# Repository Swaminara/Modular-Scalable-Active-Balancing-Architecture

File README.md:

# Modular-Scalable-Active-Balancing-Architecture

This repository contains the PCB design files of a modular scalable active cell balancing architecture proposed during my tenure as Research Associate in TUM CREATE. 

The PCBs are designed using Easily Accessible Graphical Layout Editor (EAGLE) 7.1.0 for windows. 
However, other versions of the software shall also be used for viewing and further modifying the design.

Scientific journals supporting the repository and explaining its working principle are submitted and under review process.

This repository is protected under the MIT license as attached in the repository.

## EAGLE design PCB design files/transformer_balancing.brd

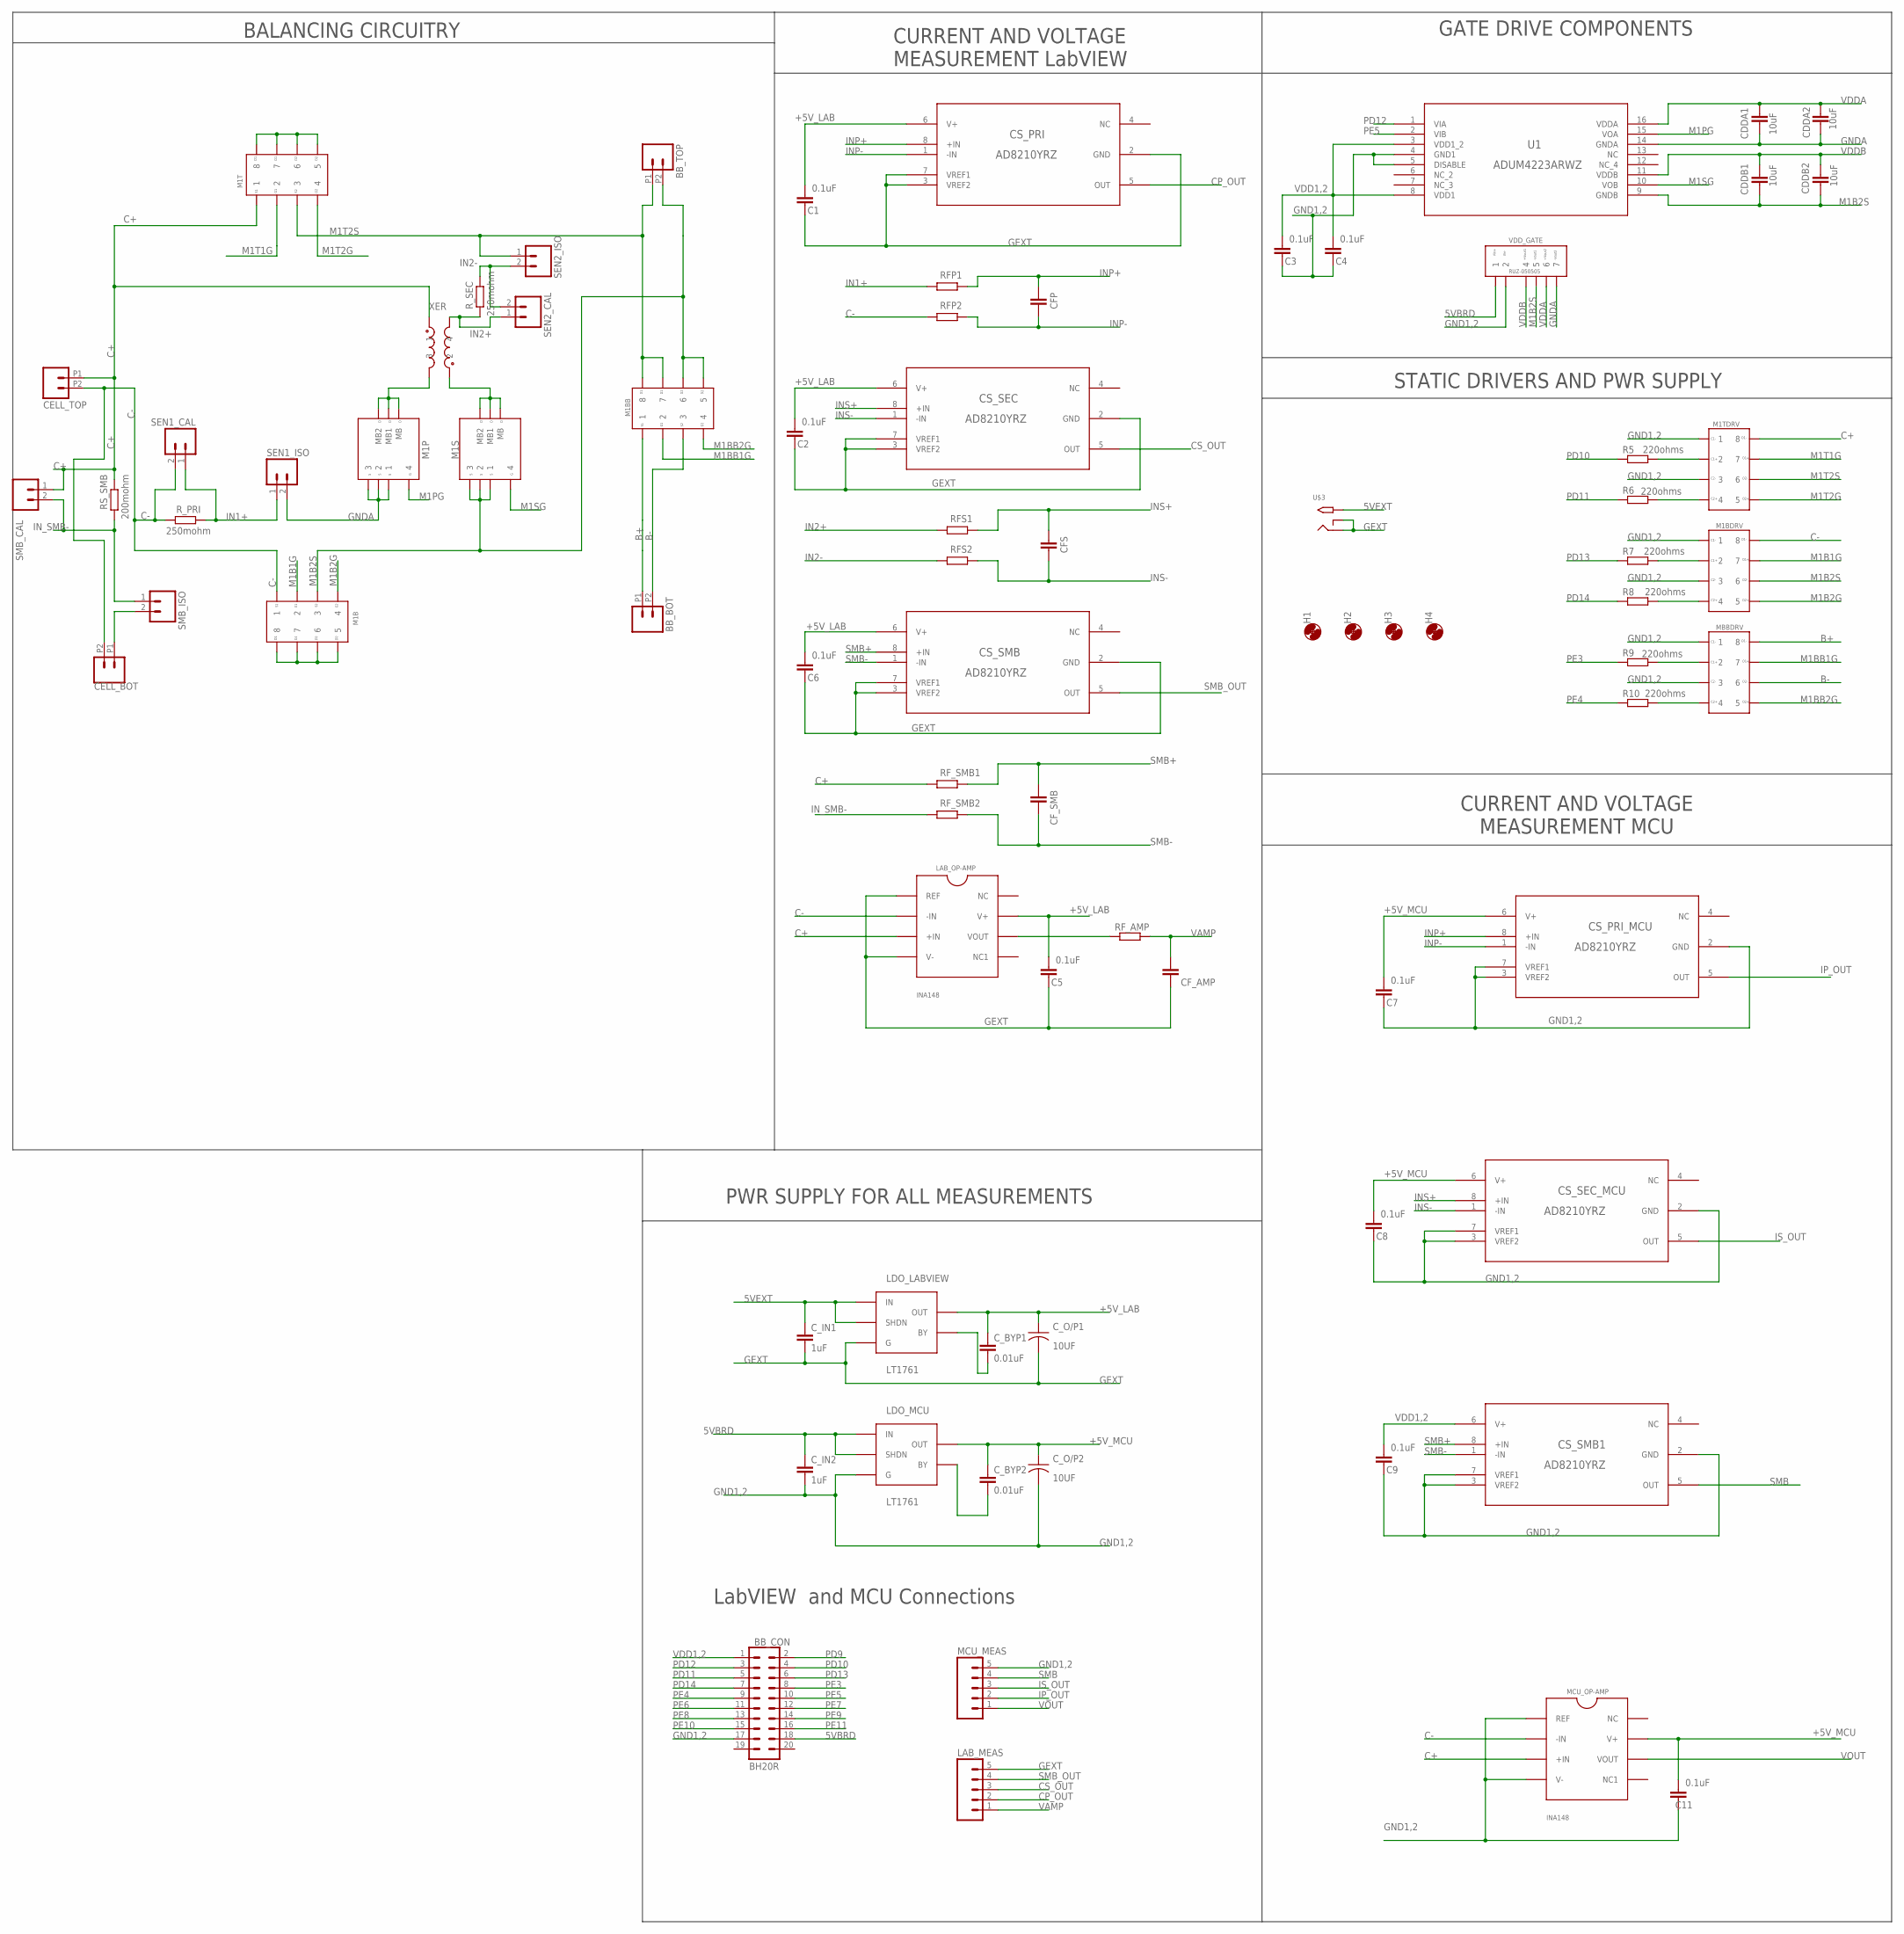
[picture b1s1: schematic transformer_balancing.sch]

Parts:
BB_BOT: M022.54MM_SCREWTERM; 1X02_2.54_SCREWTERM
BB_CON: BH20R
BB_TOP: M022.54MM_SCREWTERM; 1X02_2.54_SCREWTERM
C1, C2, C3, C4, C5, C6, C7, C8, C9, C11: 0.1uF; C0603
CDDA1, CDDA2: 10uF; C0603
CDDB1, CDDB2: 10uF; C0603
CELL_BOT: M022.54MM_SCREWTERM; 1X02_2.54_SCREWTERM
CELL_TOP: M022.54MM_SCREWTERM; 1X02_2.54_SCREWTERM
CFP: C-EUC0603; C0603
CFS: C-EUC0603; C0603
CF_AMP: C-EUC0603; C0603
CF_SMB: C-EUC0603; C0603
CS_PRI: AD8210YRZ; R_8
CS_PRI_MCU: AD8210YRZ; R_8
CS_SEC: AD8210YRZ; R_8
CS_SEC_MCU: AD8210YRZ; R_8
CS_SMB, CS_SMB1: AD8210YRZ; R_8
C_BYP1, C_BYP2: 0.01uF; C0402
C_IN1, C_IN2: 1uF; C0402
C_O/P1, C_O/P2: 10UF; 10UF_O/P_CAP_LDO
H1, H2, H3, H4: MOUNT-HOLE3.0; 3,0
LAB_MEAS: M05PTH; 1X05
LAB_OP-AMP: INA148
LDO_LABVIEW: LT1761
LDO_MCU: LT1761
M1B, M1BB, M1T: 2_CHANNEL_MOSFET
M1BDRV, M1TDRV: VOA1263
M1P, M1S: SWITCHING_MOSFET
MBBDRV: VOA1263
MCU_MEAS: M05PTH; 1X05
MCU_OP-AMP: INA148
R5, R6, R7, R8, R9, R10: 220ohms; R0603
RFP1, RFP2: 5R; R0603
RFS1, RFS2: 5R; R0603
RF_AMP: R-EU_R0603; R0603
RF_SMB1, RF_SMB2: 5R; R0603
RS_SMB: 200mohm; R0603
R_PRI: 250mohm; R0603
R_SEC: 250mohm; R0603
SEN1_CAL, SEN1_ISO, SEN2_CAL, SEN2_ISO: M02PTH; 1X02
SMB_CAL: M02PTH; 1X02
SMB_ISO: M02PTH; 1X02
U1: ADUM4223ARWZ; RW_16
U$3: 2.1MMJACK; PJ-102A
VDD_GATE: RUZ-050505
XER: COUPLED_INDUCTOR

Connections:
5VBRD: BB_CON.18, C_IN2.1, LDO_MCU.1 (IN), LDO_MCU.3 (SHDN), VDD_GATE.1
5VEXT: C_IN1.1, LDO_LABVIEW.1 (IN), LDO_LABVIEW.3 (SHDN), U$3.TIP
+5V_LAB: C1.1, C2.1, C5.1, C6.1, CS_PRI.6 (V+), CS_SEC.6 (V+), CS_SMB.6 (V+), C_BYP1.1, C_O/P1.1 (3), LAB_OP-AMP.V+, LDO_LABVIEW.5 (OUT)
+5V_MCU: C7.1, C8.1, C11.1, CS_PRI_MCU.6 (V+), CS_SEC_MCU.6 (V+), C_BYP2.1, C_O/P2.1 (3), LDO_MCU.5 (OUT), MCU_OP-AMP.V+
B+: BB_BOT.P1 (1), M1BB.1, MBBDRV.8
B-: BB_BOT.P2 (2), M1BB.3, MBBDRV.6
C+: CELL_TOP.P1 (1), LAB_OP-AMP.+IN, M1T.1, M1TDRV.8, MCU_OP-AMP.+IN, RF_SMB1.1, RS_SMB.1, SMB_CAL.1, XER.1
C-: CELL_BOT.P2 (2), CELL_TOP.P2 (2), LAB_OP-AMP.-IN, M1B.1, M1BDRV.8, MCU_OP-AMP.-IN, RFP2.1, R_PRI.2, SEN1_CAL.2
CP_OUT: CS_PRI.5 (OUT), LAB_MEAS.2
CS_OUT: CS_SEC.5 (OUT), LAB_MEAS.3
GEXT: C1.2, C2.2, C5.2, C6.2, CF_AMP.2, CS_PRI.2 (GND), CS_PRI.3 (VREF2), CS_PRI.7 (VREF1), CS_SEC.2 (GND), CS_SEC.3 (VREF2), CS_SEC.7 (VREF1), CS_SMB.2 (GND), CS_SMB.3 (VREF2), CS_SMB.7 (VREF1), C_IN1.2, C_O/P1.2 (4), LAB_MEAS.5, LAB_OP-AMP.REF, LAB_OP-AMP.V-, LDO_LABVIEW.2 (G), U$3.RING, U$3.RING_SW
GND1,2: BB_CON.17, C3.2, C4.2, C7.2, C8.2, C9.2, C11.2, CS_PRI_MCU.2 (GND), CS_PRI_MCU.3 (VREF2), CS_PRI_MCU.7 (VREF1), CS_SEC_MCU.2 (GND), CS_SEC_MCU.3 (VREF2), CS_SEC_MCU.7 (VREF1), CS_SMB1.2 (GND), CS_SMB1.3 (VREF2), CS_SMB1.7 (VREF1), C_IN2.2, C_O/P2.2 (4), LDO_MCU.2 (G), M1BDRV.1, M1BDRV.3, M1TDRV.1, M1TDRV.3, MBBDRV.1, MBBDRV.3, MCU_MEAS.5, MCU_OP-AMP.REF, MCU_OP-AMP.V-, U1.4 (GND1), U1.5 (DISABLE), VDD_GATE.2
GNDA: CDDA1.2, CDDA2.2, M1P.1, M1P.2, M1P.3, SEN1_ISO.2, U1.14 (GNDA), VDD_GATE.7
IN1+: RFP1.1, R_PRI.1, SEN1_CAL.1, SEN1_ISO.1
IN2+: RFS1.1, R_SEC.2, SEN2_CAL.1, XER.4
IN2-: RFS2.1, R_SEC.1, SEN2_CAL.2, SEN2_ISO.2
INP+: CFP.1, CS_PRI.8 (+IN), CS_PRI_MCU.8 (+IN), RFP1.2
INP-: CFP.2, CS_PRI.1 (-IN), CS_PRI_MCU.1 (-IN), RFP2.2
INS+: CFS.1, CS_SEC.8 (+IN), CS_SEC_MCU.8 (+IN), RFS1.2
INS-: CFS.2, CS_SEC.1 (-IN), CS_SEC_MCU.1 (-IN), RFS2.2
IN_SMB-: RF_SMB2.1, RS_SMB.2, SMB_CAL.2, SMB_ISO.1
IP_OUT: CS_PRI_MCU.5 (OUT), MCU_MEAS.2
IS_OUT: CS_SEC_MCU.5 (OUT), MCU_MEAS.3
M1B1G: M1B.2, M1BDRV.7
M1B2G: M1B.4, M1BDRV.5
M1B2S: BB_TOP.P2 (2), CDDB1.2, CDDB2.2, M1B.3, M1BB.5, M1BB.6, M1BDRV.6, M1S.1, M1S.2, M1S.3, U1.9 (GNDB), VDD_GATE.5
M1BB1G: M1BB.2, MBBDRV.7
M1BB2G: M1BB.4, MBBDRV.5
M1PG: M1P.4, U1.15 (VOA)
M1SG: M1S.4, U1.10 (VOB)
M1T1G: M1T.2, M1TDRV.7
M1T2G: M1T.4, M1TDRV.5
M1T2S: BB_TOP.P1 (1), M1BB.7, M1BB.8, M1T.3, M1TDRV.6, SEN2_ISO.1
unnamed: M1T.5, M1T.6, M1T.7, M1T.8
unnamed: M1TDRV.2, R5.2
unnamed: M1P.MB, M1P.MB1, M1P.MB2, XER.3
unnamed: M1TDRV.4, R6.2
unnamed: M1B.5, M1B.6, M1B.7, M1B.8
unnamed: MBBDRV.2, R9.2
unnamed: M1S.MB, M1S.MB1, M1S.MB2, XER.2
unnamed: MBBDRV.4, R10.2
unnamed: M1BDRV.4, R8.2
unnamed: LAB_OP-AMP.VOUT, RF_AMP.1
unnamed: M1BDRV.2, R7.2
unnamed: CELL_BOT.P1 (1), SMB_ISO.2
unnamed: C_BYP1.2, LDO_LABVIEW.4 (BY)
unnamed: C_BYP2.2, LDO_MCU.4 (BY)
PD9: BB_CON.2
PD10: BB_CON.4, R5.1
PD11: BB_CON.5, R6.1
PD12: BB_CON.3, U1.1 (VIA)
PD13: BB_CON.6, R7.1
PD14: BB_CON.7, R8.1
PE3: BB_CON.8, R9.1
PE4: BB_CON.9, R10.1
PE5: BB_CON.10, U1.2 (VIB)
PE6: BB_CON.11
PE7: BB_CON.12
PE8: BB_CON.13
PE9: BB_CON.14
PE10: BB_CON.15
PE11: BB_CON.16
SMB: CS_SMB1.5 (OUT), MCU_MEAS.4
SMB+: CF_SMB.1, CS_SMB.8 (+IN), CS_SMB1.8 (+IN), RF_SMB1.2
SMB-: CF_SMB.2, CS_SMB.1 (-IN), CS_SMB1.1 (-IN), RF_SMB2.2
SMB_OUT: CS_SMB.5 (OUT), LAB_MEAS.4
VAMP: CF_AMP.1, LAB_MEAS.1, RF_AMP.2
VDD1,2: BB_CON.1, C3.1, C4.1, C9.1, CS_SMB1.6 (V+), U1.3 (VDD1_2), U1.8 (VDD1)
VDDA: CDDA1.1, CDDA2.1, U1.16 (VDDA), VDD_GATE.6
VDDB: CDDB1.1, CDDB2.1, U1.11 (VDDB), VDD_GATE.4
VOUT: MCU_MEAS.1, MCU_OP-AMP.VOUT

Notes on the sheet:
BALANCING CIRCUITRY
CURRENT AND VOLTAGE MEASUREMENT LabVIEW
GATE DRIVE COMPONENTS
STATIC DRIVERS AND PWR SUPPLY
LabVIEW and MCU Connections
PWR SUPPLY FOR ALL MEASUREMENTS
CURRENT AND VOLTAGE MEASUREMENT MCU

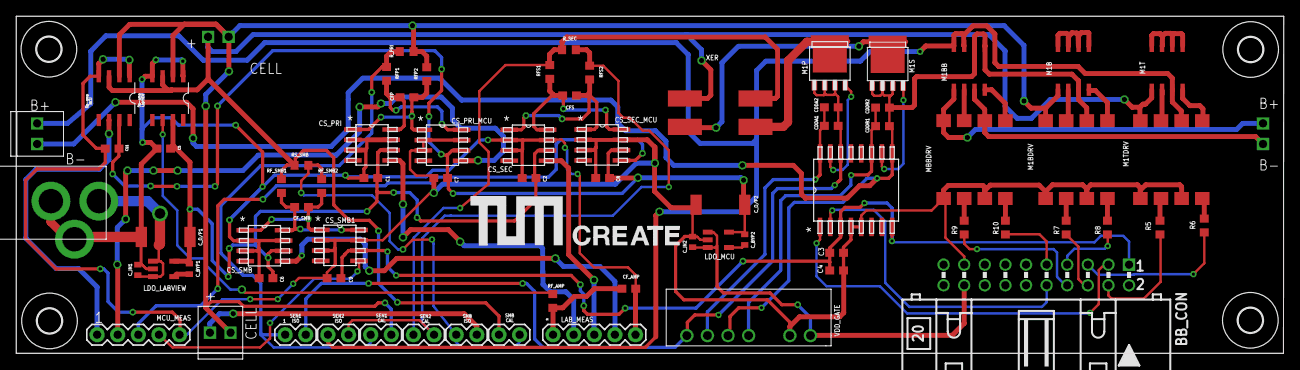
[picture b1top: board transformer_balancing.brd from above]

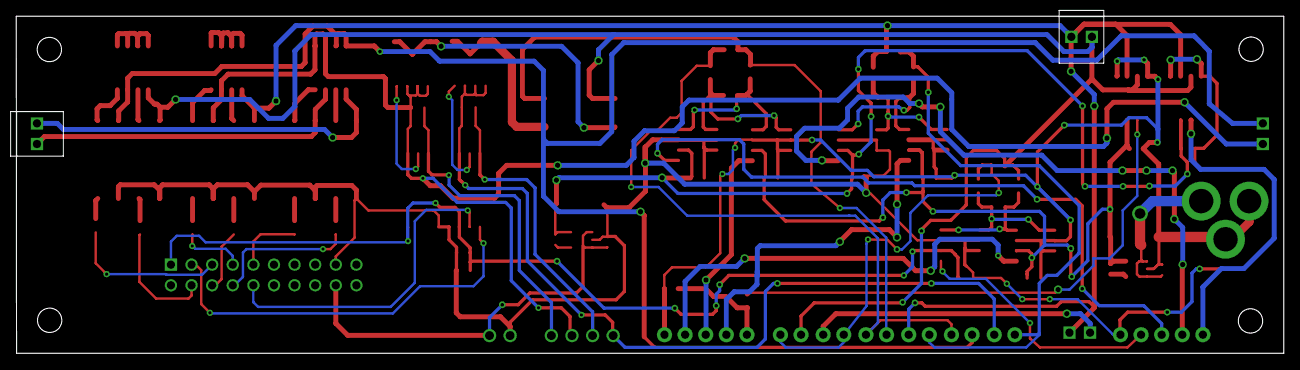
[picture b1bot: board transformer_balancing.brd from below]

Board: 2 copper layers, 156.2 x 41.5 mm, 80 parts (2 on the bottom side), 64 nets.

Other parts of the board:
U$1: BIGGER_LOGO

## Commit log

2016-02-19 Added author names in the license file, modified read me and added the design files to the repository
2016-02-23 Updated readme files

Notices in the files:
parts and their libraries:
SparkFun-Connectors: Licensing: CC v3.0 Share-Alike You are welcome to use this library for commercial purposes.
